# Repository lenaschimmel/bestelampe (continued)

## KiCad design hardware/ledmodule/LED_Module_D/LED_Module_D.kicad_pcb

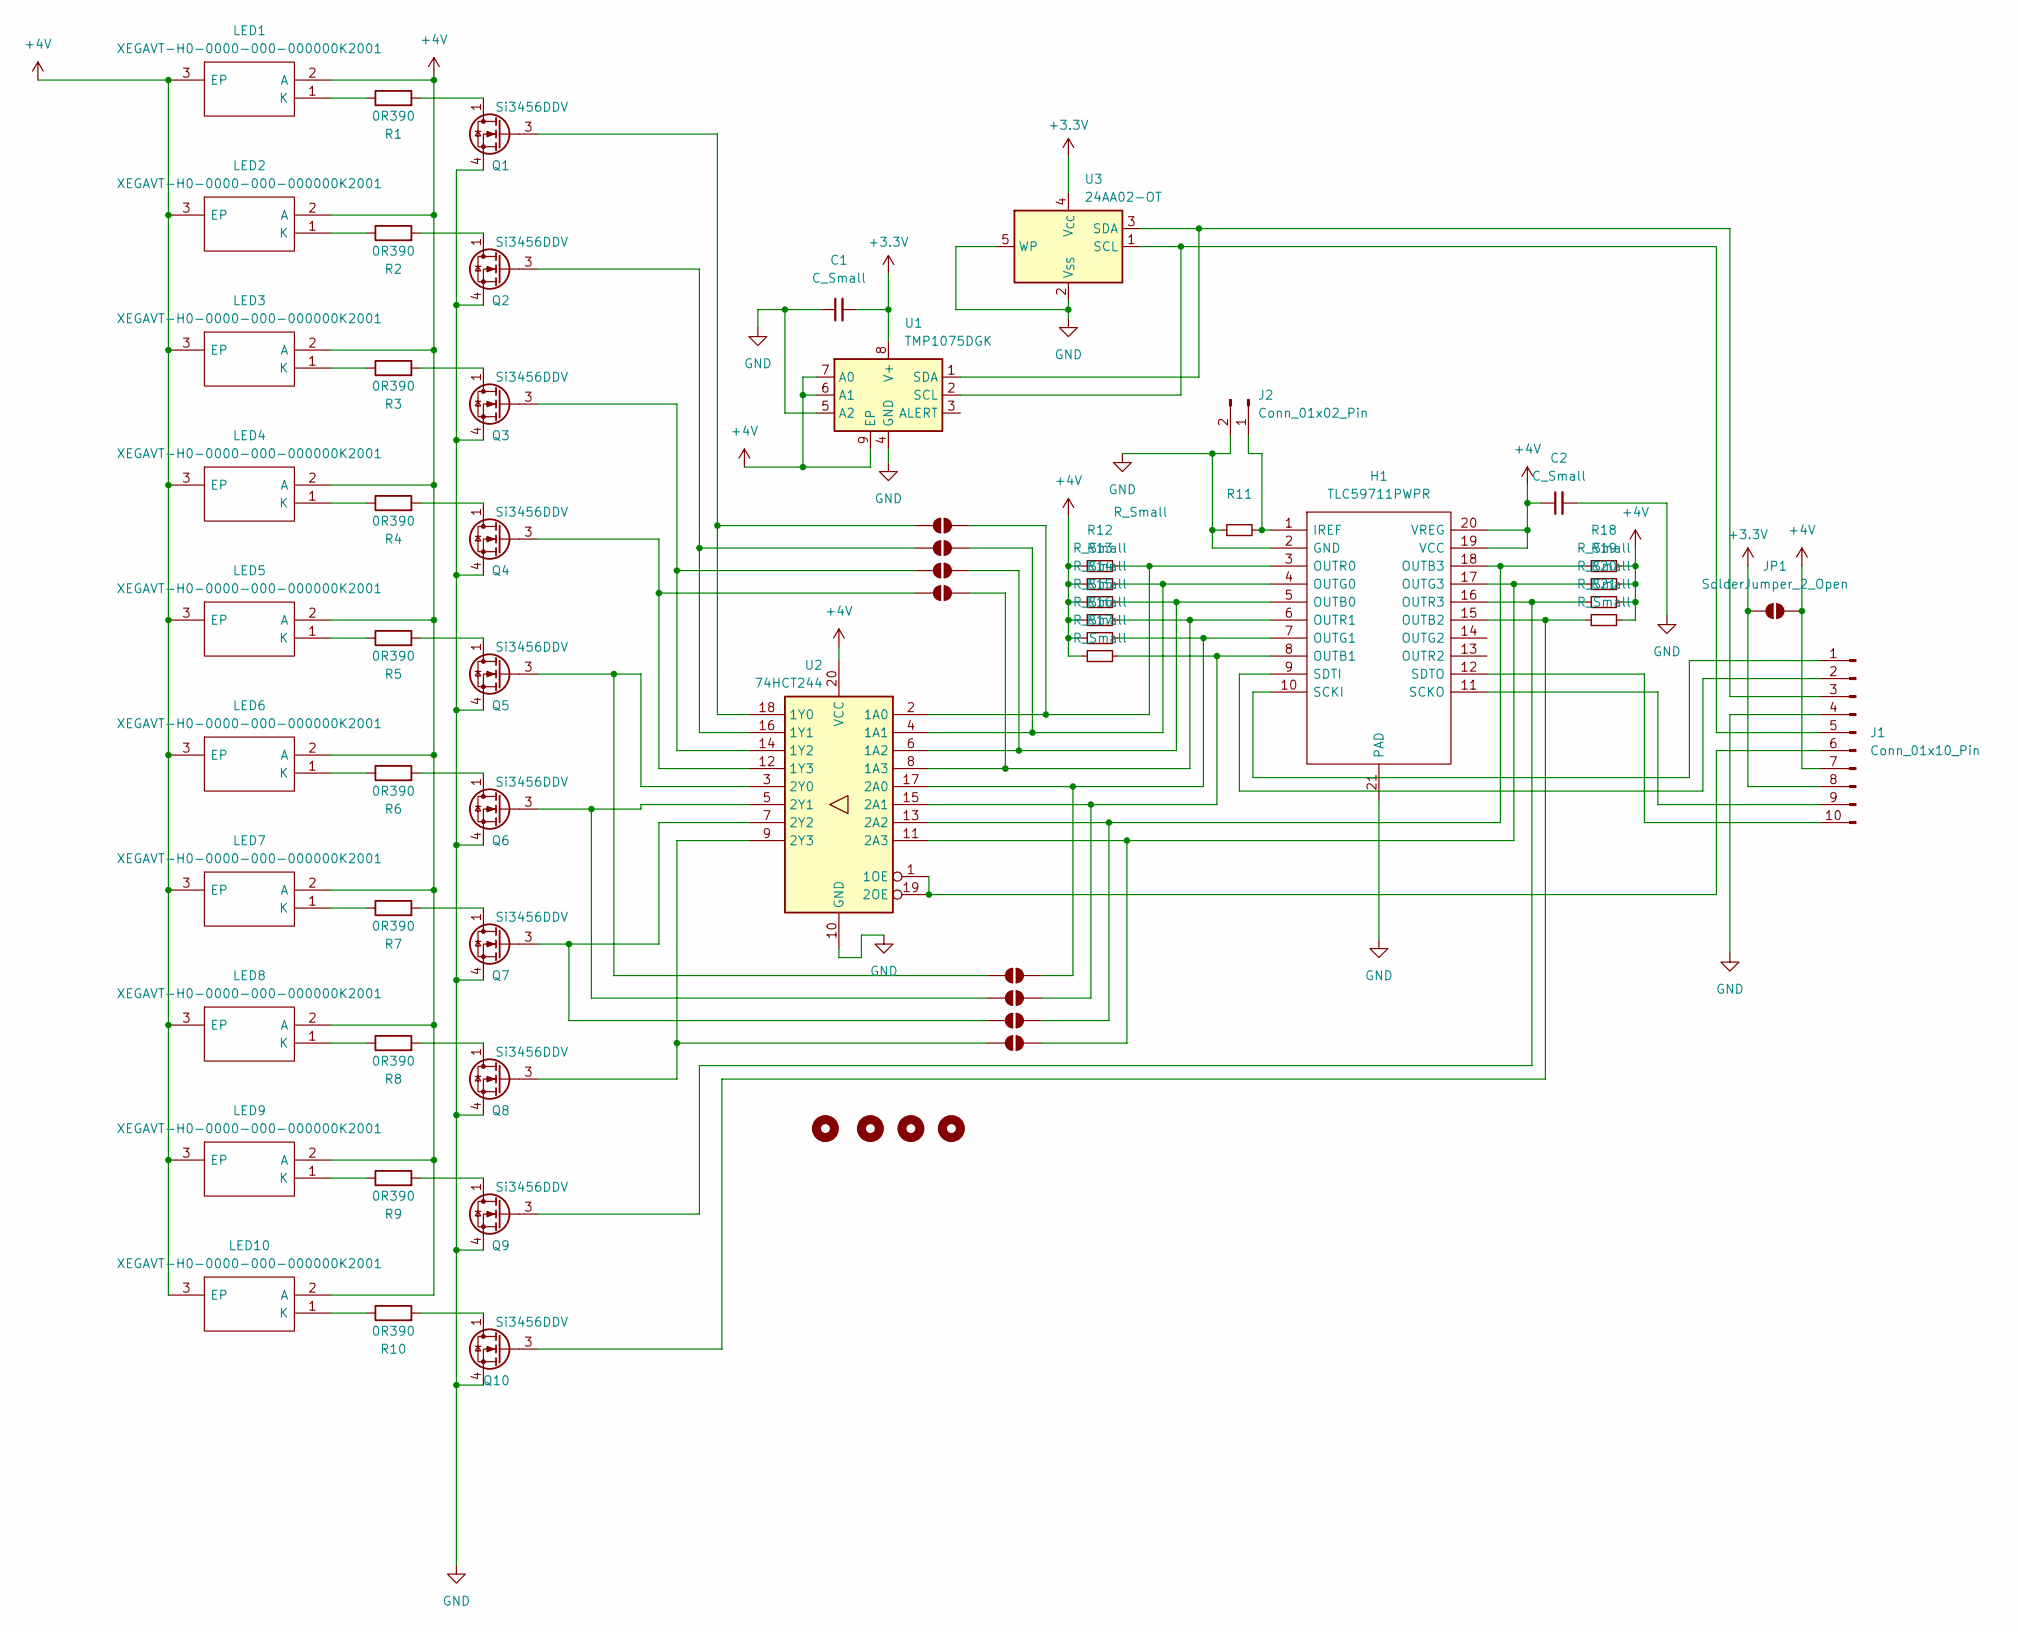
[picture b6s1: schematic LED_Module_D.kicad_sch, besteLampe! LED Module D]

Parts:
C1, C2: C_Small; C_0402_1005Metric
H1: TLC59711PWPR; SOP65P640X120-21N; Mouser Part Number 595-TLC59711PWPR
H2, H3, H4, H5: MountingHole; MountingHole_2.2mm_M2
J1: Conn_01x10_Pin; PinHeader_1x10_P2.54mm_Vertical
J2: Conn_01x02_Pin; PinHeader_1x02_P2.54mm_Vertical
JP1, JP2, JP3, JP4, JP5, JP6, JP7, JP8, JP9: SolderJumper_2_Open; SolderJumper-2_Open_RoundedPad_small
LED1, LED2, LED3, LED4, LED5, LED6, LED7, LED8, LED9, LED10: XEGAVT-H0-0000-000-000000K2001; XEGAVTH_clean; Manufacturer_Part_Number XEGAVT-H0-0000-000-000000K2001
Q1, Q2, Q3, Q4, Q5, Q6, Q7, Q8, Q9, Q10: Si3456DDV; TSOP-6_1.65x3.05mm_P0.95mm
R1, R2, R3, R4, R5, R6, R7, R8, R9, R10: 0R390; R_1020_2550Metric
R11, R12, R13, R14, R15, R16, R17, R18, R19, R20, R21: R_Small; R_0402_1005Metric
U1: TMP1075DGK; WSON-8-1EP_2x2mm_P0.5mm_EP0.9x1.6mm_ThermalVias
U2: 74HCT244; SOIC-20W_7.5x12.8mm_P1.27mm
U3: 24AA02-OT; SOT-23-5

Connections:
+3.3V: C1.2, J1.8, JP1.1 (A), U1.8 (V+), U3.4 (V_{CC})
+4V: C2.1, H1.19 (VCC), H1.20 (VREG), J1.7, JP1.2 (B), LED1.2 (A), LED1.3 (EP), LED2.2 (A), LED2.3 (EP), LED3.2 (A), LED3.3 (EP), LED4.2 (A), LED4.3 (EP), LED5.2 (A), LED5.3 (EP), LED6.2 (A), LED6.3 (EP), LED7.2 (A), LED7.3 (EP), LED8.2 (A), LED8.3 (EP), LED9.2 (A), LED9.3 (EP), LED10.2 (A), LED10.3 (EP), R12.1, R13.1, R14.1, R15.1, R16.1, R17.1, R18.2, R19.2, R20.2, R21.2, U1.6 (A1), U1.7 (A0), U1.9 (EP), U2.20 (VCC)
GND: C1.1, C2.2, H1.2 (GND), H1.21 (PAD), J1.4, J2.2, Q1.4 (S), Q2.4 (S), Q3.4 (S), Q4.4 (S), Q5.4 (S), Q6.4 (S), Q7.4 (S), Q8.4 (S), Q9.4 (S), Q10.4 (S), R11.1, U1.4 (GND), U1.5 (A2), U2.10 (GND), U3.2 (V_{SS}), U3.5 (WP)
unnamed: H1.1 (IREF), J2.1, R11.2
unnamed: H1.5 (OUTB0), JP7.2 (B), R14.2, U2.6 (1A2)
unnamed: H1.8 (OUTB1), JP4.2 (B), R17.2, U2.15 (2A1)
unnamed: H1.15 (OUTB2), Q10.3 (G), R21.1
unnamed: H1.18 (OUTB3), JP3.2 (B), R18.1, U2.13 (2A2)
unnamed: H1.4 (OUTG0), JP8.2 (B), R13.2, U2.4 (1A1)
unnamed: H1.7 (OUTG1), JP5.2 (B), R16.2, U2.17 (2A0)
unnamed: H1.17 (OUTG3), JP2.2 (B), R19.1, U2.11 (2A3)
unnamed: H1.3 (OUTR0), JP9.2 (B), R12.2, U2.2 (1A0)
unnamed: H1.6 (OUTR1), JP6.2 (B), R15.2, U2.8 (1A3)
unnamed: H1.16 (OUTR3), Q9.3 (G), R20.1
unnamed: H1.10 (SCKI), J1.1
unnamed: H1.11 (SCKO), J1.9
unnamed: H1.9 (SDTI), J1.2
unnamed: H1.12 (SDTO), J1.10
unnamed: J1.3, U1.1 (SDA), U3.3 (SDA)
unnamed: J1.5, U1.2 (SCL), U3.1 (SCL)
unnamed: J1.6, U2.1 (1OE), U2.19 (2OE)
unnamed: JP2.1 (A), Q8.3 (G), U2.9 (2Y3)
unnamed: JP3.1 (A), Q7.3 (G), U2.7 (2Y2)
unnamed: JP4.1 (A), Q6.3 (G), U2.5 (2Y1)
unnamed: JP5.1 (A), Q5.3 (G), U2.3 (2Y0)
unnamed: JP6.1 (A), Q4.3 (G), U2.12 (1Y3)
unnamed: JP7.1 (A), Q3.3 (G), U2.14 (1Y2)
unnamed: JP8.1 (A), Q2.3 (G), U2.16 (1Y1)
unnamed: JP9.1 (A), Q1.3 (G), U2.18 (1Y0)
unnamed: LED1.1 (K), R1.1
unnamed: LED2.1 (K), R2.1
unnamed: LED3.1 (K), R3.1
unnamed: LED4.1 (K), R4.1
unnamed: LED5.1 (K), R5.1
unnamed: LED6.1 (K), R6.1
unnamed: LED7.1 (K), R7.1
unnamed: LED8.1 (K), R8.1
unnamed: LED9.1 (K), R9.1
unnamed: LED10.1 (K), R10.1
unnamed: Q1.1 (D), Q1.2 (D), Q1.5 (D), Q1.6 (D), R1.2
unnamed: Q2.1 (D), Q2.2 (D), Q2.5 (D), Q2.6 (D), R2.2
unnamed: Q3.1 (D), Q3.2 (D), Q3.5 (D), Q3.6 (D), R3.2
unnamed: Q4.1 (D), Q4.2 (D), Q4.5 (D), Q4.6 (D), R4.2
unnamed: Q5.1 (D), Q5.2 (D), Q5.5 (D), Q5.6 (D), R5.2
unnamed: Q6.1 (D), Q6.2 (D), Q6.5 (D), Q6.6 (D), R6.2
unnamed: Q7.1 (D), Q7.2 (D), Q7.5 (D), Q7.6 (D), R7.2
unnamed: Q8.1 (D), Q8.2 (D), Q8.5 (D), Q8.6 (D), R8.2
unnamed: Q9.1 (D), Q9.2 (D), Q9.5 (D), Q9.6 (D), R9.2
unnamed: Q10.1 (D), Q10.2 (D), Q10.5 (D), Q10.6 (D), R10.2

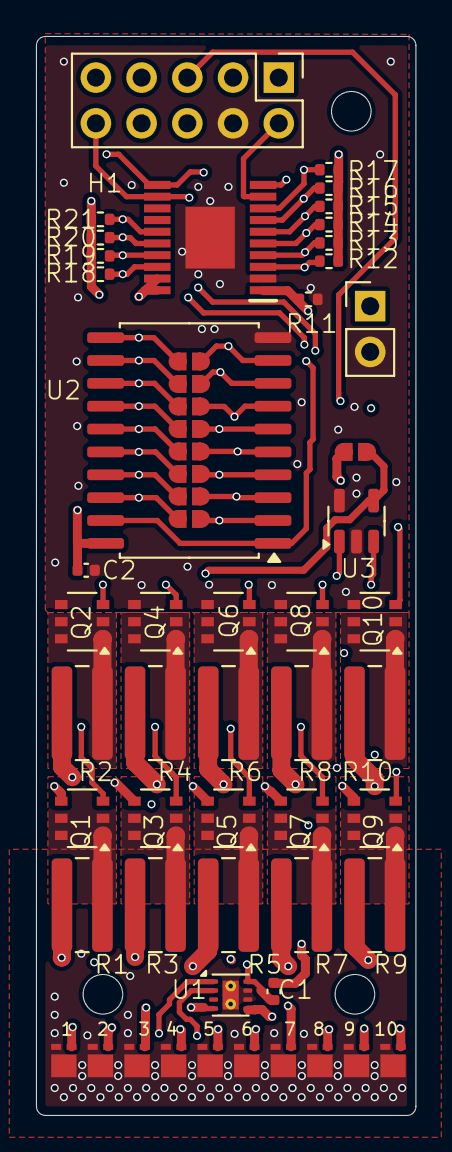
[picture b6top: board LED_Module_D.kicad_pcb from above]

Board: 4 copper layers, 21.1 x 59.9 mm, 61 parts (0 on the bottom side), 49 nets.

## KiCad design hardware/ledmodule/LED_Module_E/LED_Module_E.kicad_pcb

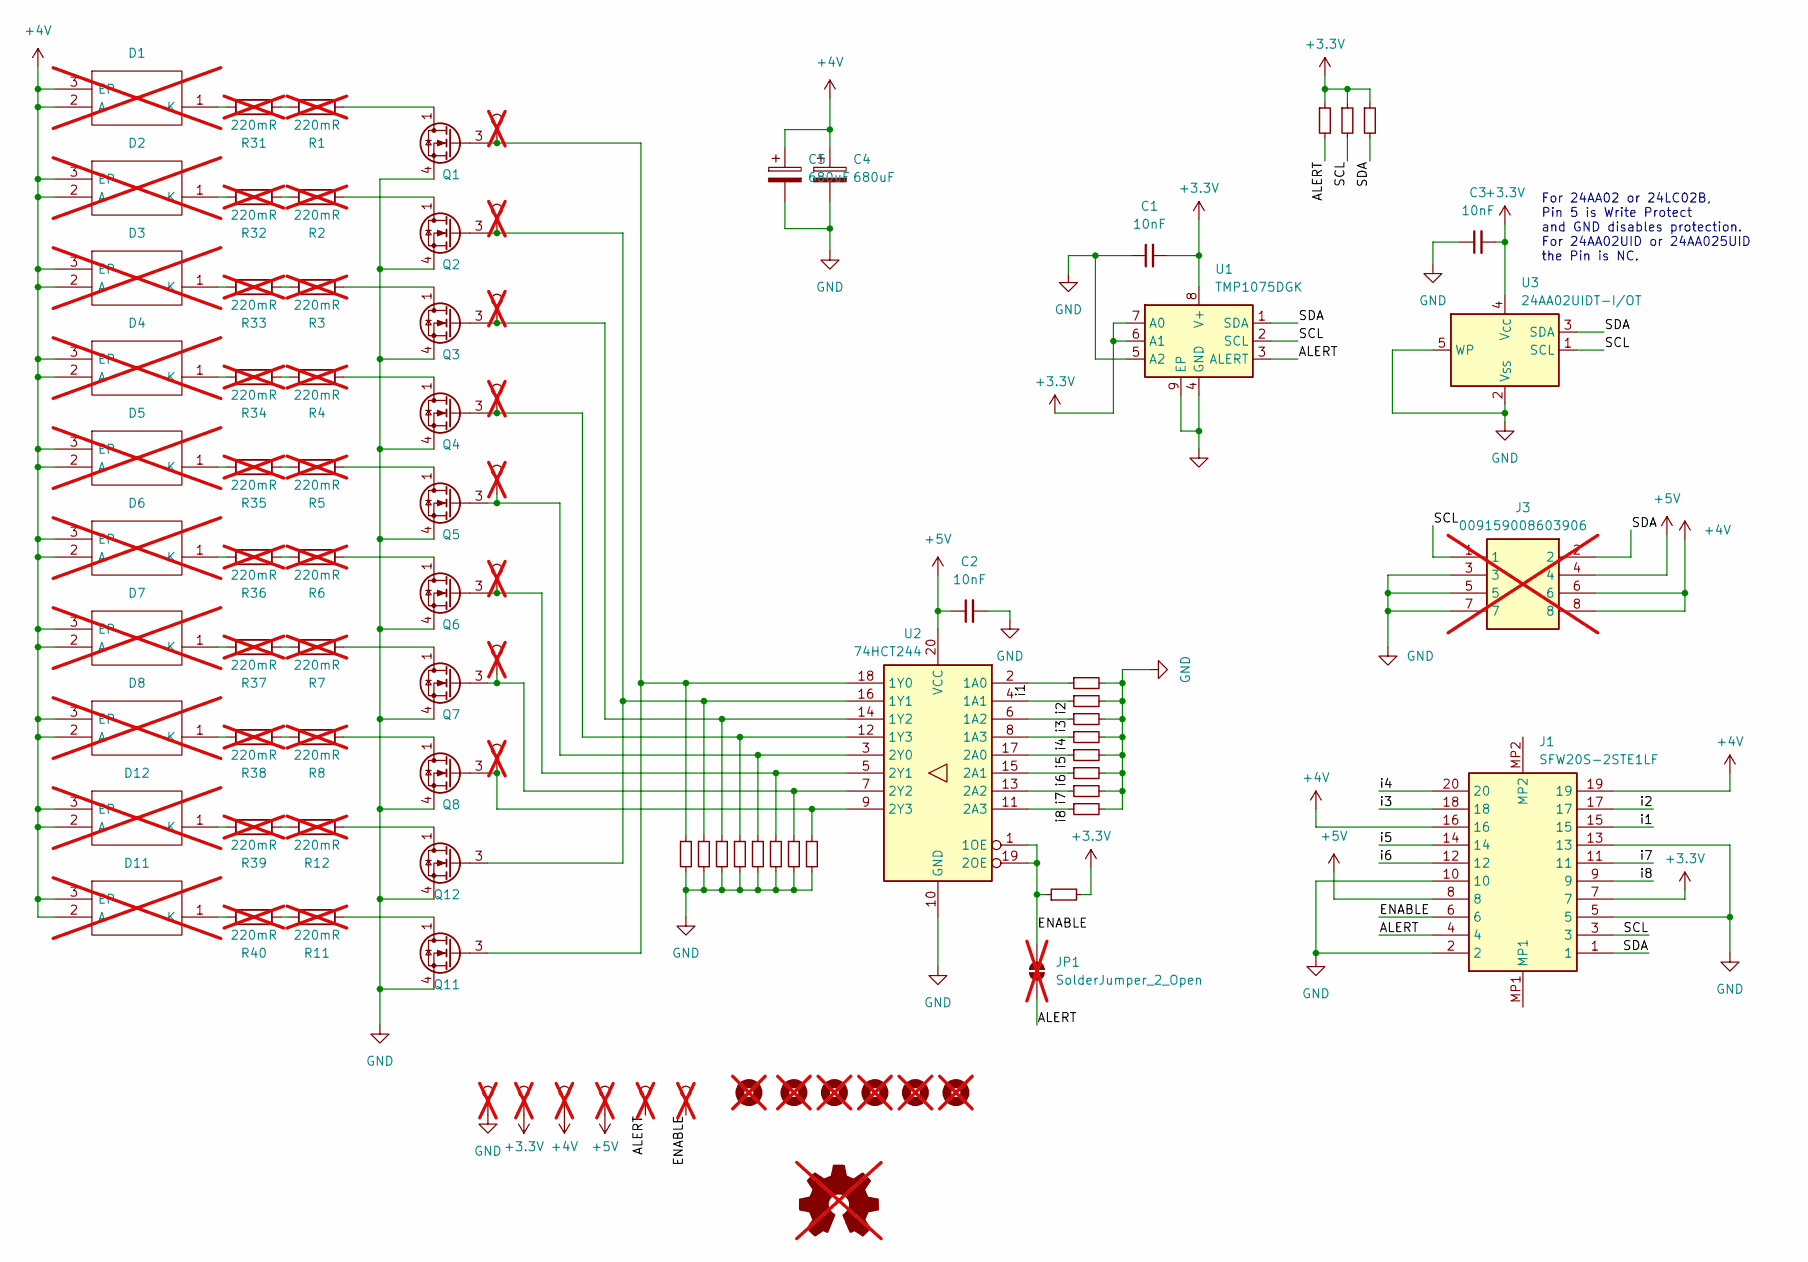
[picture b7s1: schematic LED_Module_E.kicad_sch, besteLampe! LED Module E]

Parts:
C1: 10nF; C_0402_1005Metric; Manufacturer_Part_Number CL05B103KB5NNNC; LCSC Part # C15195
C2, C3: 10nF; C_0603_1608Metric_Pad1.08x0.95mm_HandSolder; Manufacturer_Part_Number 0603B103K500NT; LCSC Part # C57112
C4, C5: 680uF; CP_Elec_10x7.9; Manufacturer_Part_Number RVT1A681M0810 680UF 10V; LCSC Part # C2760485
D1, D2, D3, D4, D5, D6, D7, D8, D11, D12: XEGAVT-H0-0000-000-000000K2001; XEGAVTH_clean; Manufacturer_Part_Number XEGAVT-H0-0000-000-000000K2001; not fitted
H1, H2, H3, H4, H5, H6: MountingHole; MountingHole_3.2mm_M3; not fitted
J1: SFW20S-2STE1LF; SFW20S2STE1LF; Manufacturer_Part_Number SFW20S-2STE1LF; LCSC Part # C5407823
J3: 009159008603906; Mouser Part Number 581-009159008603906; not fitted
JP1: SolderJumper_2_Open; SolderJumper-2_P1.3mm_Open_TrianglePad1.0x1.5mm; not fitted
LOGO1: Logo_Open_Hardware_Small; OSHW-Logo_5.7x6mm_SilkScreen; not fitted
Q1, Q2, Q3, Q4, Q5, Q6, Q7, Q8, Q11, Q12: Si3456DDV; TSOP-6_1.65x3.05mm_P0.95mm; Manufacturer_Part_Number SI3456DDV-T1-GE3; LCSC Part # C145273
R1, R2, R3, R4, R5, R6, R7, R8, R11, R12, R31, R32, R33, R34, R35, R36, R37, R38, R39, R40: 220mR; R_1020_2550Metric; not fitted
R9, R10, R13, R14, R15, R16, R17, R18, R19, R20, R21, R22, R23, R24, R25, R26, R27, R28, R29, R30: 2740R; R_0603_1608Metric; Manufacturer_Part_Number 0603WAF2701T5E; LCSC Part # C13167
TP1, TP2, TP3, TP4, TP5, TP6, TP7, TP8, TP9, TP10, TP11, TP12, TP13, TP14: TestPoint; TestPoint_Pad_D1.0mm; not fitted
U1: TMP1075DGK; VSSOP-8_3.0x3.0mm_P0.65mm; Manufacturer_Part_Number TMP1075DGKR; LCSC Part # C2864807
U2: 74HCT244; SOIC-20W_7.5x12.8mm_P1.27mm; Manufacturer_Part_Number SI3456DDV-T1-GE3; LCSC Part # C5978
U3: 24AA02UIDT-I/OT; SOT-23-5; Manufacturer_Part_Number 24AA02UIDT-I/OT; LCSC Part # C511274

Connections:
+3.3V: C1.2, C3.2, J1.7, R19.2, R28.1, R29.1, R30.1, TP2.1, U1.6 (A1), U1.7 (A0), U1.8 (V+), U3.4 (V_{CC})
+4V: C4.1, C5.1, D1.2 (A), D1.3 (EP), D2.2 (A), D2.3 (EP), D3.2 (A), D3.3 (EP), D4.2 (A), D4.3 (EP), D5.2 (A), D5.3 (EP), D6.2 (A), D6.3 (EP), D7.2 (A), D7.3 (EP), D8.2 (A), D8.3 (EP), D11.2 (A), D11.3 (EP), D12.2 (A), D12.3 (EP), J1.16, J1.19, J3.6, J3.8, TP3.1
+5V: C2.1, J1.8, J3.4, TP4.1, U2.20 (VCC)
/ALERT: J1.4, JP1.1 (A), R28.2, TP5.1, U1.3 (ALERT)
/ENABLE: J1.6, JP1.2 (B), R19.1, TP6.1, U2.1 (1OE), U2.19 (2OE)
/SCL: J1.3, J3.1, R29.2, U1.2 (SCL), U3.1 (SCL)
/SDA: J1.1, J3.2, R30.2, U1.1 (SDA), U3.3 (SDA)
/i1: J1.15, R9.1, U2.2 (1A0)
/i2: J1.17, R10.1, U2.4 (1A1)
/i3: J1.18, R13.1, U2.6 (1A2)
/i4: J1.20, R14.1, U2.8 (1A3)
/i5: J1.14, R15.1, U2.17 (2A0)
/i6: J1.12, R16.1, U2.15 (2A1)
/i7: J1.11, R17.1, U2.13 (2A2)
/i8: J1.9, R18.1, U2.11 (2A3)
GND: C1.1, C2.2, C3.1, C4.2, C5.2, J1.2, J1.5, J1.10, J1.13, J3.3, J3.5, J3.7, Q1.4 (S), Q2.4 (S), Q3.4 (S), Q4.4 (S), Q5.4 (S), Q6.4 (S), Q7.4 (S), Q8.4 (S), Q11.4 (S), Q12.4 (S), R9.2, R10.2, R13.2, R14.2, R15.2, R16.2, R17.2, R18.2, R20.2, R21.2, R22.2, R23.2, R24.2, R25.2, R26.2, R27.2, TP1.1, U1.4 (GND), U1.5 (A2), U1.9 (EP), U2.10 (GND), U3.2 (V_{SS}), U3.5 (WP)
unnamed: D1.1 (K), R31.1
unnamed: D2.1 (K), R32.1
unnamed: D3.1 (K), R33.1
unnamed: D4.1 (K), R34.1
unnamed: D5.1 (K), R35.1
unnamed: D6.1 (K), R36.1
unnamed: D7.1 (K), R37.1
unnamed: D8.1 (K), R38.1
unnamed: D11.1 (K), R40.1
unnamed: D12.1 (K), R39.1
unnamed: Q1.1 (D), Q1.2 (D), Q1.5 (D), Q1.6 (D), R1.2
unnamed: Q1.3 (G), Q11.3 (G), R20.1, TP7.1, U2.18 (1Y0)
unnamed: Q2.1 (D), Q2.2 (D), Q2.5 (D), Q2.6 (D), R2.2
unnamed: Q3.1 (D), Q3.2 (D), Q3.5 (D), Q3.6 (D), R3.2
unnamed: Q3.3 (G), R22.1, TP9.1, U2.14 (1Y2)
unnamed: Q4.1 (D), Q4.2 (D), Q4.5 (D), Q4.6 (D), R4.2
unnamed: Q4.3 (G), R23.1, TP10.1, U2.12 (1Y3)
unnamed: Q5.1 (D), Q5.2 (D), Q5.5 (D), Q5.6 (D), R5.2
unnamed: Q5.3 (G), R24.1, TP11.1, U2.3 (2Y0)
unnamed: Q6.1 (D), Q6.2 (D), Q6.5 (D), Q6.6 (D), R6.2
unnamed: Q6.3 (G), R25.1, TP12.1, U2.5 (2Y1)
unnamed: Q7.1 (D), Q7.2 (D), Q7.5 (D), Q7.6 (D), R7.2
unnamed: Q7.3 (G), R26.1, TP13.1, U2.7 (2Y2)
unnamed: Q8.1 (D), Q8.2 (D), Q8.5 (D), Q8.6 (D), R8.2
unnamed: Q8.3 (G), R27.1, TP14.1, U2.9 (2Y3)
unnamed: Q11.1 (D), Q11.2 (D), Q11.5 (D), Q11.6 (D), R11.2
unnamed: Q12.1 (D), Q12.2 (D), Q12.5 (D), Q12.6 (D), R12.2
unnamed: Q2.3 (G), Q12.3 (G), R21.1, TP8.1, U2.16 (1Y1)
unnamed: R1.1, R31.2
unnamed: R2.1, R32.2
unnamed: R3.1, R33.2
unnamed: R11.1, R40.2
unnamed: R12.1, R39.2
unnamed: R4.1, R34.2
unnamed: R5.1, R35.2
unnamed: R6.1, R36.2
unnamed: R7.1, R37.2
unnamed: R8.1, R38.2

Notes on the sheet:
For 24AA02 or 24LC02B, Pin 5 is Write Protect and GND disables protection. For 24AA02UID or 24AA025UID the Pin is NC.

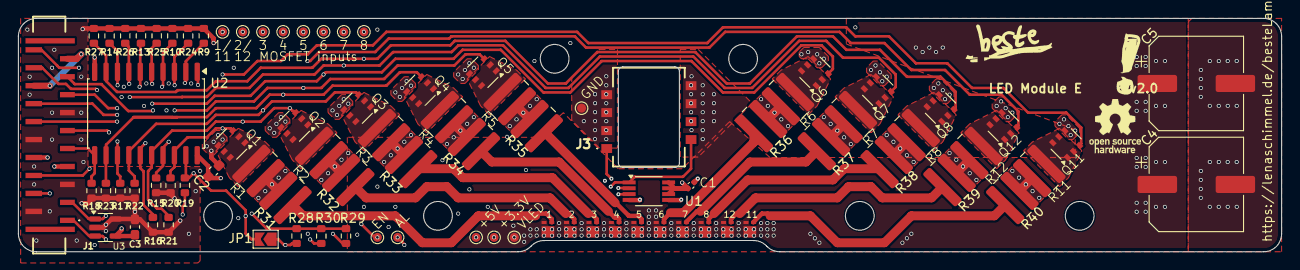
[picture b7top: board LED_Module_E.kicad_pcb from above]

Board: 4 copper layers, 140.8 x 26.0 mm, 92 parts (0 on the bottom side), 54 nets.
